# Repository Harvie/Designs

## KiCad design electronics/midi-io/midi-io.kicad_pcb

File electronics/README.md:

# Harvie's electro projects
Some schematics, PCB designs and other electronics related stuff
  * http://blog.harvie.cz/
  * http://wiki.spoje.net/

### Usefull Software
  * http://www.gpleda.org/
  * http://www.falstad.com/circuit/
  * http://www.cadsoftusa.com/ (Eagle CAD)

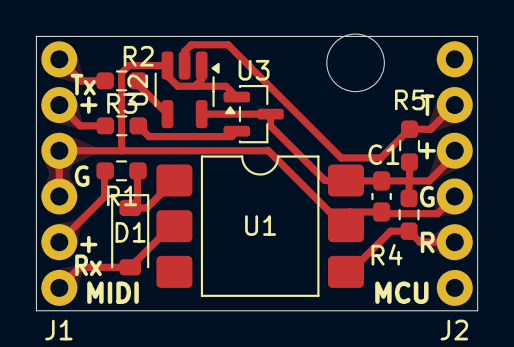
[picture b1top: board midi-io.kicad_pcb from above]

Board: 2 copper layers, 24.5 x 15.2 mm, 13 parts (0 on the bottom side), 11 nets.

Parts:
C1: 100nF; C_0603_1608Metric_Pad1.08x0.95mm_HandSolder
D1: 1N4148W; D_SOD-123
H1: MountingHole; MountingHole_3.2mm_M3
J1: MIDI; PinHeader_1x06_P2.54mm_Vertical
J2: MCU; PinHeader_1x06_P2.54mm_Vertical
R1: 220R; R_0603_1608Metric_Pad0.98x0.95mm_HandSolder
R2: 10R; R_0603_1608Metric_Pad0.98x0.95mm_HandSolder
R3: 33R; R_0603_1608Metric_Pad0.98x0.95mm_HandSolder
R4: 470R; R_0603_1608Metric_Pad0.98x0.95mm_HandSolder
R5: 10K; R_0603_1608Metric_Pad0.98x0.95mm_HandSolder
U1: H11L1SR2M; SMDIP-6_W9.53mm
U2: 74LVC1G07; SOT-23-5_HandSoldering
U3: MCP1700x-330xxTT; SOT-23

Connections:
GND: C1.2, J1.3, J1.4, J2.3, U1.5, U2.1 (NC), U2.3 (GND), U3.1 (GND)
unnamed: D1.1 (K), R1.1, U1.1
unnamed: R2.2, U2.4
unnamed: R3.2, U3.2 (VO)
RX: J2.2, R4.2, U1.4
RX+: J1.2, R1.2
RX-: D1.2 (A), J1.1, U1.2
TX: J2.5, R5.1, U2.2
TX+: J1.5, R3.1
TX-: J1.6, R2.1
VCC: C1.1, J2.4, R4.1, R5.2, U1.6, U2.5 (VCC), U3.3 (VI)

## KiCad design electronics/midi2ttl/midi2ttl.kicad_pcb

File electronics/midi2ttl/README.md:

# midi2ttl — MIDI IN/OUT interface (monotribe / 3.3V / 5V)

Compact KiCad MIDI interface board: opto-isolated **MIDI IN**, resistor **MIDI OUT**, and a 6-pin host header matching the Korg monotribe internal serial connector. Host VCC may be **3.3 V or 5 V** with no regulator or level shifter.

## Host / monotribe pinout (JST-PH 6P “Serial”)

| Pin | Name | Board pad | Notes |
|-----|------|-----------|--------|
| 1 | /BOOT | `HOST_BOOT` | Not used (pad only) |
| 2 | RXD0 | `HOST_RX` | From optocoupler MIDI IN |
| 3 | TXD0 | `HOST_TX` | To MIDI OUT resistors |
| 4 | VCC | `HOST_VCC` | 3.3 V on monotribe; 3.3/5 V on MCU reuse |
| 5 | GND | `HOST_GND` | |
| 6 | SCK1 | `HOST_SCK` | Not used (pad only) |

Sources: [beatnic / monotribe notes](https://beatnic.jp/takedanotes/vol31/), [Gameboy Genius MIDI mod](https://blog.gg8.se/wordpress/2011/08/14/monotribe-midi-and-me/).

## Circuit

- **MIDI IN:** DIN pins 4/5 → 220 Ω + antiparallel 1N4148W into **H11L1SR2M** Schmitt optocoupler (works 3–15 V). Open-collector VO pulled up with 470 Ω to host VCC → `RX`.
- **MIDI OUT:** `VCC`—220 Ω—DIN4, `TX`—220 Ω—DIN5, DIN2 = GND. 220 Ω is MIDI-standard and works at 3.3 V with modern receivers (H11L1 threshold ~1.6 mA).
- **Why H11L1 (not 6N138):** Reliable at 3.3 V; Schmitt output; no bias resistor. 6N138 is poorly specified at 3.3 V and caused zipper noise on monotribe mods.

Connectors are **off-board**: THT wire pads with dual strain-relief holes. Two **M3** mounting holes.

## JLCPCB PCBA

Files in `fab/`:

| File | Use |
|------|-----|
| `midi2ttl-gerbers.zip` | PCB order (Gerber + drill) |
| `BOM-JLCPCB.csv` | Assembly BOM |
| `CPL-JLCPCB.csv` | Pick-and-place (SMT only) |
| `midi2ttl-schematic.pdf` | Schematic |

### Parts

| Ref | Part | LCSC | Library |
|-----|------|------|---------|
| U1 | H11L1SR2M | **C20082** | Extended (~$3 feeder on Economic) |
| R1,R3,R4 | 220 Ω 0603 1% | **C22962** | Basic |
| R2 | 470 Ω 0603 1% | **C23179** | Basic |
| C1 | 100 nF 0603 | **C14663** | Basic |
| D1 | 1N4148W SOD-123 | **C81598** | Basic |

Only U1 is Extended; passives are Basic (0 feeder fee). THT wire pads / mounting holes are hand-soldered (not in CPL).

## Wiring DIN5 (solder side)

MIDI pin numbering is easy to swap. Solder side with notch up:

- Pin 4 = current source / “+”
- Pin 5 = current sink / signal
- Pin 2 = shield/GND (OUT only)

## Regen

```bash
python3 scripts/generate_project.py
```

Opens in KiCad 10 (`midi2ttl.kicad_pro`).

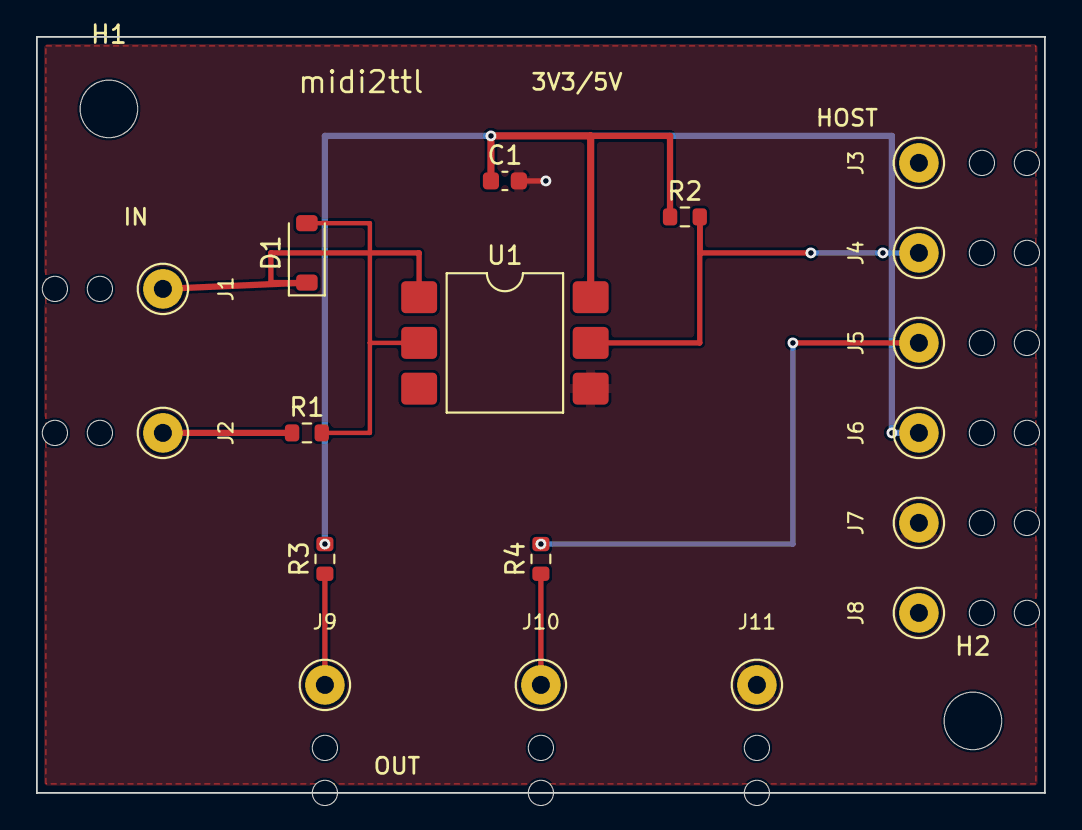
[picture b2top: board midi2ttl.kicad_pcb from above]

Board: 2 copper layers, 56.0 x 42.0 mm, 20 parts (0 on the bottom side), 9 nets.

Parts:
C1: 100nF; C_0603_1608Metric
D1: 1N4148W; D_SOD-123
H1, H2: MountingHole_3.2mm_M3
J1: IN4; WirePad_THT_Relief
J2: IN5; WirePad_THT_Relief
J3: BOOT; WirePad_THT_Relief
J4: RX; WirePad_THT_Relief
J5: TX; WirePad_THT_Relief
J6: VCC; WirePad_THT_Relief
J7: GND; WirePad_THT_Relief
J8: SCK; WirePad_THT_Relief
J9: OUT4; WirePad_THT_Relief
J10: OUT5; WirePad_THT_Relief
J11: OUT2; WirePad_THT_Relief
R1, R3, R4: 220; R_0603_1608Metric
R2: 470; R_0603_1608Metric
U1: H11L1SR2M; SMDIP-6_W9.53mm

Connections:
GND: C1.2, J7.1, J11.1, U1.4
MIDI_IN_4: D1.1, J1.1, U1.1
MIDI_IN_5: J2.1, R1.1
MIDI_OUT_4: J9.1, R3.1
MIDI_OUT_5: J10.1, R4.1
OPTO_C: D1.2, R1.2, U1.2
RX: J4.1, R2.2, U1.5
TX: J5.1, R4.2
VCC: C1.1, J6.1, R2.1, R3.2, U1.6

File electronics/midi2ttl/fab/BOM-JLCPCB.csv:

Comment,Designator,Footprint,LCSC Part #
H11L1SR2M Schmitt optocoupler SOP-6,U1,SMDIP-6_W9.53mm,C20082
220R 1% 0603,"R1,R3,R4",R_0603_1608Metric,C22962
470R 1% 0603,R2,R_0603_1608Metric,C23179
100nF 50V X7R 0603,C1,C_0603_1608Metric,C14663
1N4148W SOD-123,D1,D_SOD-123,C81598

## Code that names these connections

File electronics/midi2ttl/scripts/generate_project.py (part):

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
    ux, uy = 88.9, 57.15
    parts = [
        inst("Connector_Generic:Conn_01x01", "J1", "MIDI_IN_4", 25.4, 50.8, wire_fp, {"Description": "DIN5 pin4"}),
        inst("Connector_Generic:Conn_01x01", "J2", "MIDI_IN_5", 25.4, 63.5, wire_fp, {"Description": "DIN5 pin5"}),
        inst("Device:R", "R1", "220", 45.72, 63.5, r_fp, {"LCSC": "C22962"}, rot=90),
        inst("Diode:1N4148", "D1", "1N4148W", 63.5, 57.15, d_fp, {"LCSC": "C81598"}),
        inst("midi2ttl:H11L1SR2M", "U1", "H11L1SR2M", ux, uy, u_fp, {"LCSC": "C20082"}),
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        inst("Connector_Generic:Conn_01x01", "J8", "HOST_SCK", 139.7, 88.9, wire_fp, {"Description": "JST pin6 SCK1"}),
        inst("Device:R", "R3", "220", 177.8, 50.8, r_fp, {"LCSC": "C22962"}, rot=90),
        inst("Device:R", "R4", "220", 177.8, 63.5, r_fp, {"LCSC": "C22962"}, rot=90),
        inst("Connector_Generic:Conn_01x01", "J9", "MIDI_OUT_4", 203.2, 50.8, wire_fp, {"Description": "DIN5 pin4"}),
        inst("Connector_Generic:Conn_01x01", "J10", "MIDI_OUT_5", 203.2, 63.5, wire_fp, {"Description": "DIN5 pin5"}),
        inst("Connector_Generic:Conn_01x01", "J11", "MIDI_OUT_2", 203.2, 76.2, wire_fp, {"Description": "DIN5 pin2 GND"}),
        inst("Mechanical:MountingHole", "H1", "M3", 25.4, 101.6, mh_fp),
        inst("Mechanical:MountingHole", "H2", "M3", 203.2, 101.6, mh_fp),
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
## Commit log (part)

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2011-08-26 Added designs made before creating this repository
2011-11-17 Stupid darlington amplifier + gigabit poe injector
2011-11-17 fixed error in gigabit poe
2012-05-06 Motherboard IO shield
2012-05-10 IO Shield for GA-D525TUD Motherboard
2014-09-25 README update
2014-09-25 renamed files
2014-09-25 class d amp schematic
2014-10-07 Gigabit ethernet surge protector
2014-10-18 MOSFET full wave rectifier
2014-10-18 MOSFET_half_wave_rectifiers
2014-11-02 Active softstart for inductive loads, welders, etc...
2014-11-20 8x2 stacked RJ45 for geda PCB
2014-11-20 Better stacked RJ45
2014-11-20 poe panel begin
2014-11-20 poe panel konektory
2014-11-20 poe panel pokusy
2014-11-20 poe panel improvements
2014-11-20 poe panel layer swap
2014-11-20 clearance fix
2014-11-21 PoE panel SMD caps
2014-11-21 layers fixed
2014-11-21 experiment
2014-11-21 one more routed
2014-11-21 everything "routed"
2014-11-21 jumper wires are cleaner
2014-11-21 Layout description
2014-11-21 Protection module example
2014-11-21 made module shorter
2014-11-21 Prepared for fuse holder
2014-11-21 Fixed zener diode polarity
2014-11-21 board resize
2014-11-21 centered header
2014-11-21 Layer fix
2014-11-22 README fix
2014-11-25 Cleaned up poe panel lines
2014-11-28 rerouted using fat tracks
2014-11-28 some changes i do not remember
2014-11-28 rerouted panel again
2014-11-28 minor routing improvement
2014-11-28 fixed phantom line
2014-12-07 Inductor size
2014-12-07 Screw terminal for poe panel
2014-12-07 rerouted for 1206 caps
2015-05-25 darlington sziklai quadruple
2015-06-07 SDIP30 breakout
2015-06-07 proper export
2016-06-18 parasitic switch
2016-06-18 new parasitic
2016-07-20 shark!
2016-07-20 drop
2016-07-20 nose shark
2016-07-20 drop thru trucks
2016-07-20 gandi
2016-08-13 lvs3
2016-08-13 lvs3 fixed short
2016-08-13 fix posun
2016-08-13 tl431 with diode
2016-08-13 fix resistor
2016-08-13 comments
2016-08-13 reverse voltage
2016-08-13 moar comments
2016-08-13 hysteresis
2016-08-17 tl431 diode fix
2016-08-17 fixed to match real TL431
2016-08-17 low power
2017-08-09 low voltage shutdown
2017-08-09 deprecated
2017-08-10 test
2018-04-06 zena na slunci
2018-04-06 last few months of work
2018-04-25 cart pick
2018-04-25 deleted point
2018-05-09 kayak paddle
2018-05-14 Kayak paddle id
2018-06-26 footstop
2018-06-26 kryt
2021-02-11 Repjack B2
2021-02-12 wire clamp prototype
2021-10-04 hadice sprcha
2021-10-04 hacek
2021-10-04 nespresso molly guard
2021-10-04 auto moto
2021-10-04 krouzky
2021-10-04 sroubky
2021-10-07 Added DIN RAIL label generator
2021-10-07 Emoji
2021-10-07 Center
2021-10-07 Typo
2021-10-07 Spisovne
2021-10-07 Colspany
2021-10-07 18mm pitch
2021-10-07 Title
2021-10-07 svodic
2021-10-07 Landscape
2021-10-07 Cestina
2021-10-07 Preklepy
2021-10-07 Unifikace
2021-10-07 Emoji na copypaste
2021-10-07 Emoji fix
2021-10-07 Rezie
2021-10-07 Centrovani ikonek
2021-10-07 More emoji
2021-10-07 Robot
2021-10-07 Newliny
2021-12-06 Automatic update
2021-12-06 Pre-line
2021-12-06 Lepsi formatovatelnost
2021-12-06 Preklep
2022-04-03 wrench2
2022-04-03 color
2022-04-03 more color
2022-04-03 moar icons
2022-04-03 Freezer
2022-04-03 warning
2022-04-03 Save
2022-04-03 Print
2022-04-04 improved css
2022-04-04 Better link
2022-04-04 Better code readability
2022-04-04 colspan example
2022-04-04 English example
2022-04-04 Fixed colspans
2022-04-04 Cathegories
2022-04-04 breaker
2022-04-04 prohibido
2022-04-04 pitch
2022-04-04 SPDX
2022-04-04 Dalsi priklad
2022-04-07 Prehlednejsi
2022-04-07 konzistence
2023-10-03 rope brush
2023-10-03 Vylepseni rope brushe
2023-10-04 Lepsi hadice
2023-10-24 Lepsi klips
2023-10-29 rudo
2023-10-30 upravy
2023-11-02 nove modely
2023-11-03 lepsi pozice diry
2023-12-11 nastrel formy na kvetinac
2024-10-24 lepsi planter
2024-10-24 planter4 fix
2024-10-25 nicer shape of cavity
2024-11-10 screw holes
2024-11-10 New planter
2025-01-18 CAM turret prototype
2025-01-18 alicam
2025-01-18 progress
2025-01-18 Prvni vytistena verze turretu
2025-01-18 Druhy pokus tisk
2025-01-18 Lepsi ulozeni koule
2025-01-18 cable slit
2025-01-18 Tighter hold
2025-01-18 3. pokus tisk
2025-01-19 colors
2025-01-19 Upload na thingiverse
2025-02-08 modular idea
2025-02-09 double planter
2025-02-09 Pokus o zaformovani
2025-02-09 Oprava indexu
2025-02-09 opravena hloubka
2025-02-09 snizeny o pul cm
2025-02-10 refaktorace kodu
2025-02-10 cleanup
2025-02-10 odtok
2025-02-10 fix tloustky balkonu
2025-02-11 proper goniometry
2025-02-11 Added BOSL2
2025-02-12 prepsano do bosl2
2025-02-12 pyramida
2025-02-12 Obnoven kod pro generovani formy
2025-02-12 Odstraneno netisknutelne zaobleni
2025-02-12 Lepsi zaformovani
2025-02-12 diry na srouby
2025-02-12 doladeni sroubu
2025-02-12 zacisteni formy
2025-02-12 copyright
2025-02-12 testers
2025-02-12 Cibule na vytazeni
2025-02-12 Tisk v1
2025-02-13 inteligentnejsi umisteni sroubu
2025-02-13 uspornejsi model
2025-02-14 cavity inspector
2025-02-14 Vyrazne zoptimalizovany demolding vnitrku
2025-02-14 cavity skew
2025-02-15 Vylepsena forma
2025-02-15 todo
2025-02-15 update bosl
2025-02-16 tlakovy demolding
2025-02-17 lepsi rozvod tlaku
2025-05-20 backup artillery
2025-05-21 Prvni prototyp
2025-05-21 offset nad konektor
2025-05-21 opraveno
2025-05-22 better clamp
2025-05-23 lepsi verze
2025-05-26 krum v4
2025-05-27 domiv2
2025-05-27 krum v7
2025-05-28 ladeni v7
2025-05-31 terrain
2025-06-04 premodelovana strecha
2025-06-10 hotovo
2026-06-10 Allow indexing to continue on next row. Only reset on .indexed class
2026-06-10 square tables possible
2026-06-10 same font in all browsers
2026-06-10 smaller margins
2026-06-11 added big
2026-06-11 deploy
2026-06-11 new link
2026-06-12 17.9mm pitch
2026-06-12 configurable pitch
2026-06-12 17.85mm
